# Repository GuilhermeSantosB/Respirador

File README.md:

# Respirador
Projeto Respirador Senai 2020

PCB Kicad
Arduio Nano
Respirador

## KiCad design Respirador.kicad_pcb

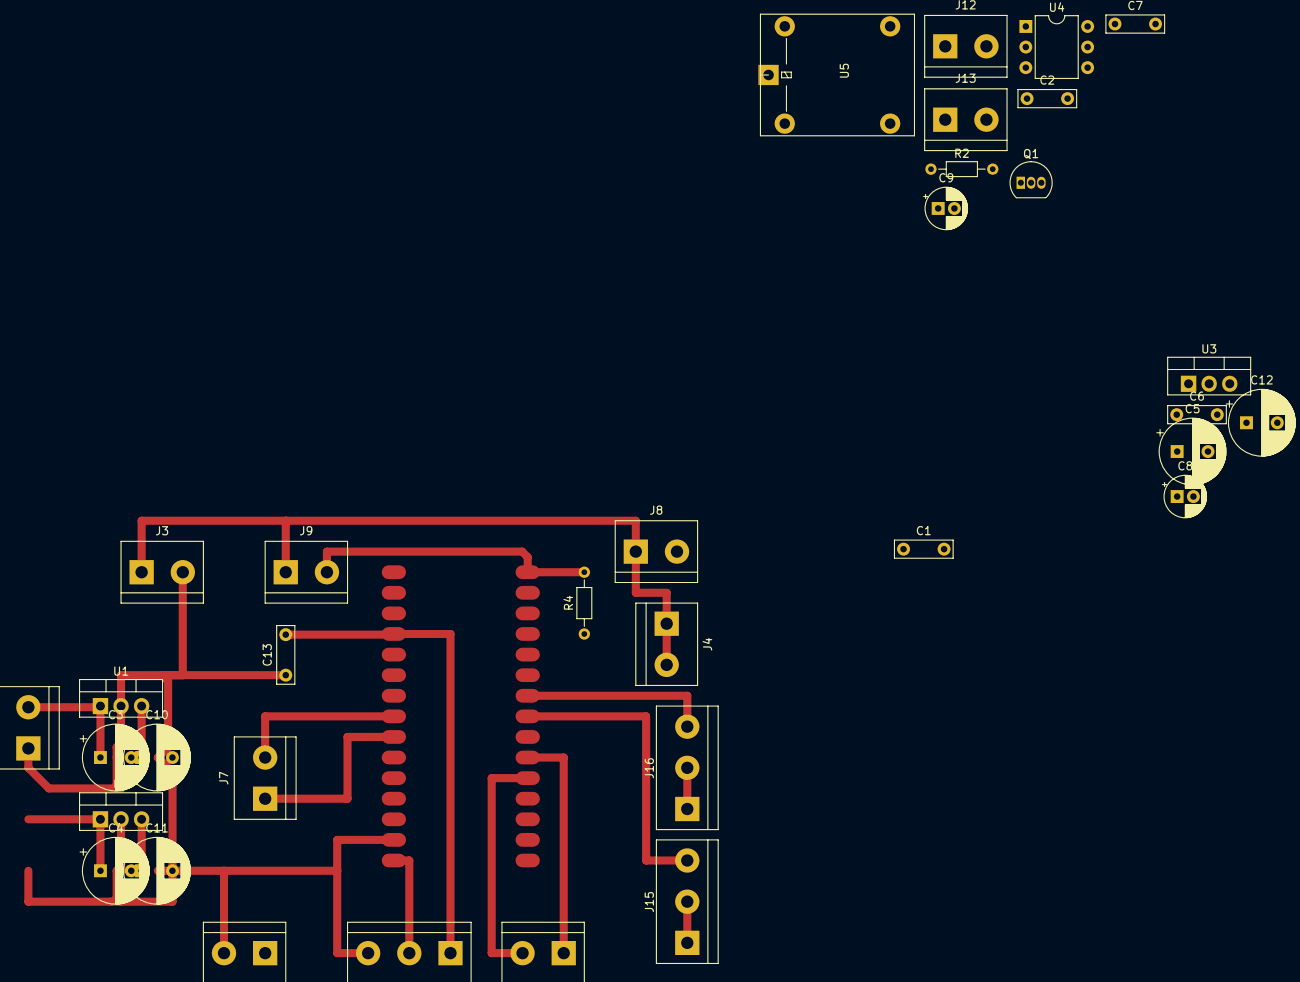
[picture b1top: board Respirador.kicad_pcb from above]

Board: 2 copper layers, 35 parts (0 on the bottom side), 18 nets.

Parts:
C1, C2: 470uF; C_Rect_L7.0mm_W2.0mm_P5.00mm
C3, C4, C5, C10, C11, C12: 100uF; CP_Radial_D8.0mm_P3.80mm
C6, C7: 100nF; C_Rect_L7.0mm_W2.0mm_P5.00mm
C8, C9: 1uF; CP_Radial_D5.0mm_P2.00mm
C13: C; C_Rect_L7.0mm_W2.0mm_P5.00mm
J1: 12V_IN; TerminalBlock_bornier-2_P5.08mm
J3: 5V_LCD; TerminalBlock_bornier-2_P5.08mm
J4: ENABLE_BTS; TerminalBlock_bornier-2_P5.08mm
J5: 5V_ENCODER; TerminalBlock_bornier-2_P5.08mm
J6: CH_ENCODER; TerminalBlock_bornier-2_P5.08mm
J7: I2C_LCD; TerminalBlock_bornier-2_P5.08mm
J8: SUPLY_BTS; TerminalBlock_bornier-2_P5.08mm
J9: BT_PIN; TerminalBlock_bornier-2_P5.08mm
J10: 5V_POT; TerminalBlock_bornier-3_P5.08mm
J12: BT_OFF; TerminalBlock_bornier-2_P5.08mm
J13: BT_ON; TerminalBlock_bornier-2_P5.08mm
J14: Arduino-NANO-33; NANO_33_Footprint_SMD_Castell
J15: ABT; TerminalBlock_bornier-3_P5.08mm
J16: FCH; TerminalBlock_bornier-3_P5.08mm
Q1: BC548; TO-92_Inline
R2, R4: 10K; R_Axial_DIN0204_L3.6mm_D1.6mm_P7.62mm_Horizontal
U1, U2, U3: L7805; TO-220-3_Vertical
U4: 4N25; DIP-6_W7.62mm
U5: AY1RC2

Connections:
5V_1: C6.1, C7.1, C8.1, C9.1, C10.1, J3.1, J4.1, J4.2, J8.1, J9.1, J10.2, J14.15, U1.3
5V_2: C11.1, J5.1, U2.3
5V_3: C12.1, U3.3
12V: C1.2, C2.2, C3.1, C3.2, C4.1, C4.2, C5.1, C5.2, C6.2, C7.2, C8.2, C9.2, C10.2, C11.2, C12.2, C13.1, J1.2, J3.2, J5.2, J8.2, J10.3, J12.2, J13.1, J13.2, J14.14, R4.1, U1.1, U1.2, U2.1, U2.2, U3.1, U3.2, U5.1, U5.4
BT_PIN: J9.2, J14.30, R4.2
BZ_1: J14.27, R2.1
ENC_CH_A: J6.1, J14.21
ENC_CH_B: J6.2, J14.20
unnamed: J14.23, J15.3
unnamed: J14.24, J16.3
unnamed: J15.1, J15.2
unnamed: J16.1, J16.2
unnamed: Q1.2, U4.4
unnamed: Q1.3, U4.2
POT_PIN: C13.2, J10.1, J14.4
SDA: J7.1, J14.8
SLC: J7.2, J14.9
SP_1: C1.1, J14.5, J14.6
